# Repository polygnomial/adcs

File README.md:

# ADCS

## Docs

- Power Architecture
- RT1170 and RT1060 pin map
- slides and other notes
- Tim's review
- TODO move other notes here

## Hardware

### Soldermander

CPU (RT1170) + RAM (MRAM - SEMC and xSPI) + power breakout board, with 2x 100-pin board to board connectors.

### Sqrt of G

Eventual functional ADCS controller and sensor mainboard that the CPU board will sit on top of

### PCBranch

Development breakout board that breaks out all the pins of the RT1170 CPU

---

## Code

### flight

Rust code with a Teensy target, RT1170 target (not yet implemented), etc.

### cpp-code

Useful for checking that I implemented my Rust drivers correctly

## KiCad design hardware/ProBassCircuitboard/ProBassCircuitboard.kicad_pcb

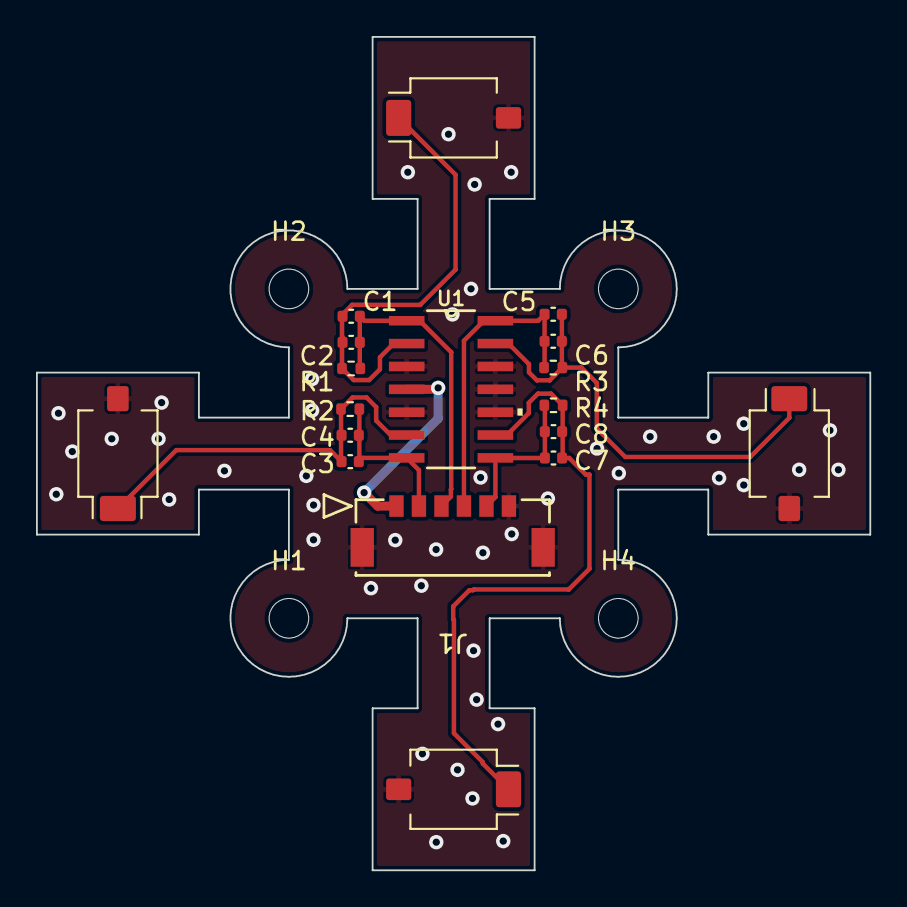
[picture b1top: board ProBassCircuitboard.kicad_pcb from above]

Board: 2 copper layers, 46.3 x 46.3 mm, 22 parts (0 on the bottom side), 10 nets.

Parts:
C1, C3, C5, C7: 1nF; C_0402_1005Metric
C2, C4, C6, C8: 100nF; C_0402_1005Metric
D1, D2, D3, D4: SFH2430; Osram_SFH2430
H1, H2, H3, H4: MountingHole_Pad; MountingHole_2.2mm_M2
J1: 5055670631; CON_5055670631
R1, R2, R3, R4: 3.9k; R_0402_1005Metric
U1: LTC2052IS_PBF; SO-14_S

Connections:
+3V3: J1.1, U1.4 (V+)
/OUT1: C1.2, C2.2, J1.3, R1.2, U1.1 (OUTA)
/OUT2: C3.2, C4.2, J1.2, R2.2, U1.7 (OUTB)
/OUT3: C7.2, C8.2, J1.5, R4.2, U1.8 (OUTC)
/OUT4: C5.2, C6.2, J1.4, R3.2, U1.14 (OUTD)
/Photodiode 1/IN-: C1.1, C2.1, D1.1 (K), R1.1, U1.2 (-INA)
/Photodiode 2/IN-: C3.1, C4.1, D2.1 (K), R2.1, U1.6 (-INB)
/Photodiode 3/IN-: C7.1, C8.1, D4.1 (K), R4.1, U1.9 (-INC)
/Photodiode 4/IN-: C5.1, C6.1, D3.1 (K), R3.1, U1.13 (-IND)
GND: D1.2 (A), D2.2 (A), D3.2 (A), D4.2 (A), J1.6, J1.7 (Shield), J1.8 (Shield), U1.3 (+INA), U1.5 (+INB), U1.10 (+INC), U1.11 (V-), U1.12 (+IND)

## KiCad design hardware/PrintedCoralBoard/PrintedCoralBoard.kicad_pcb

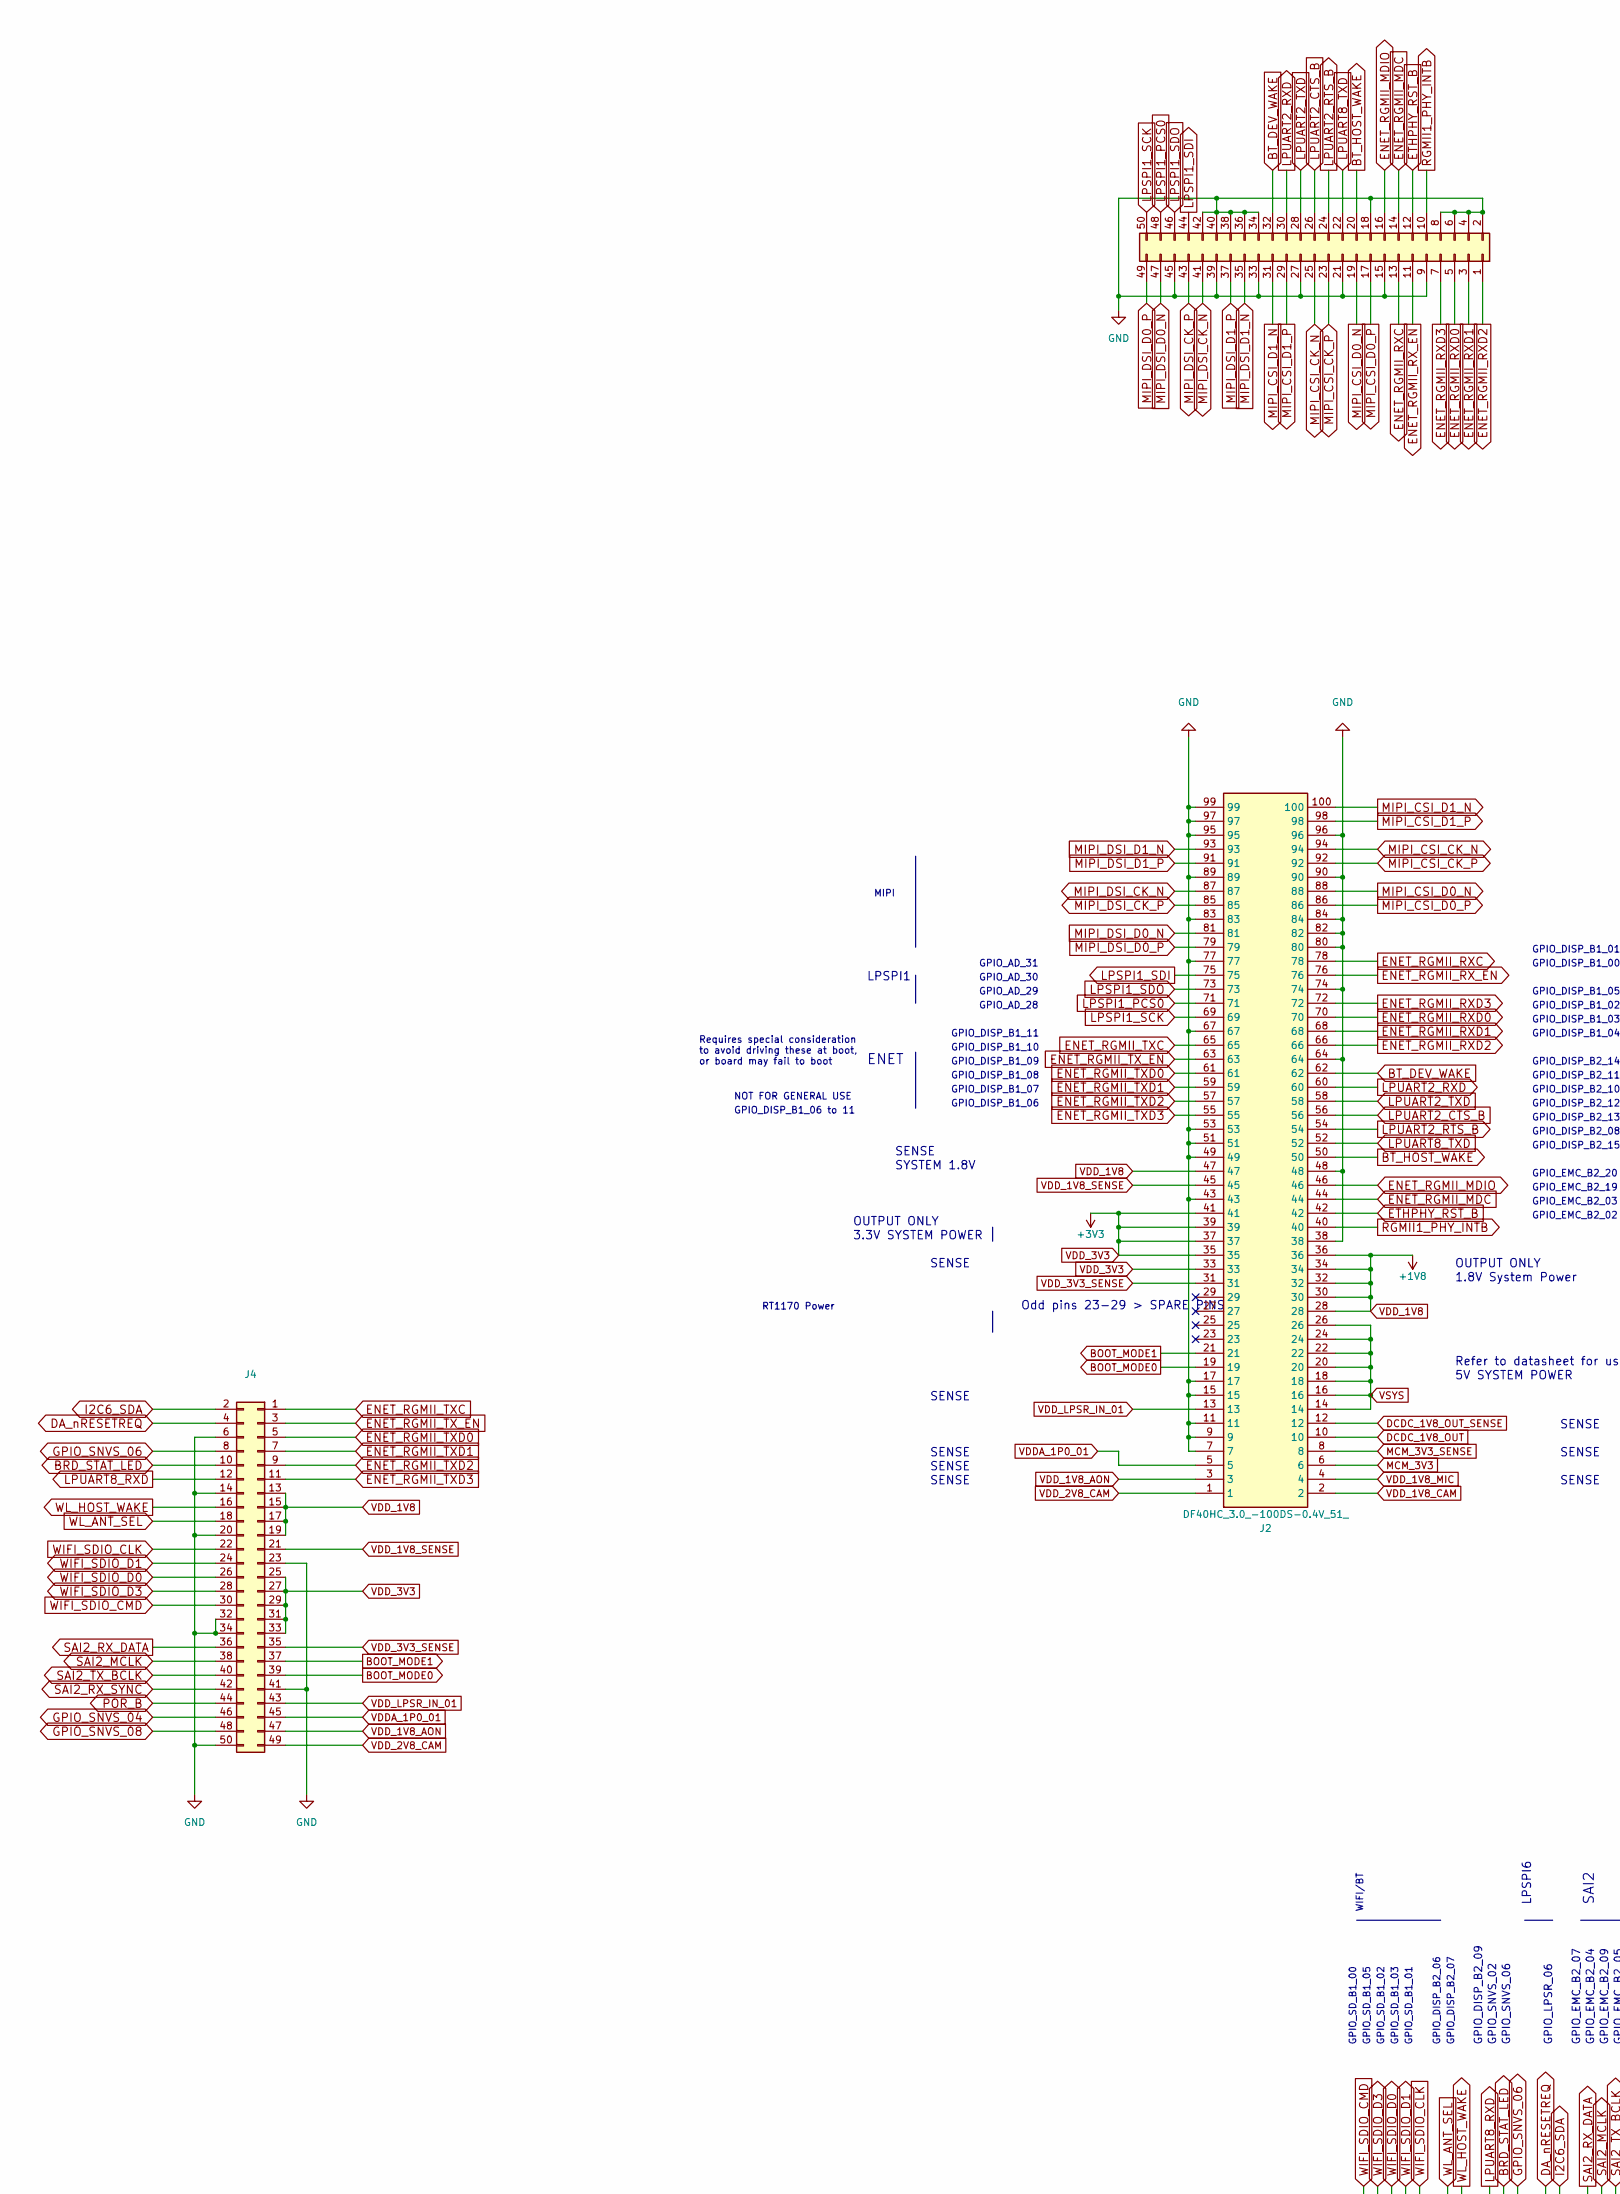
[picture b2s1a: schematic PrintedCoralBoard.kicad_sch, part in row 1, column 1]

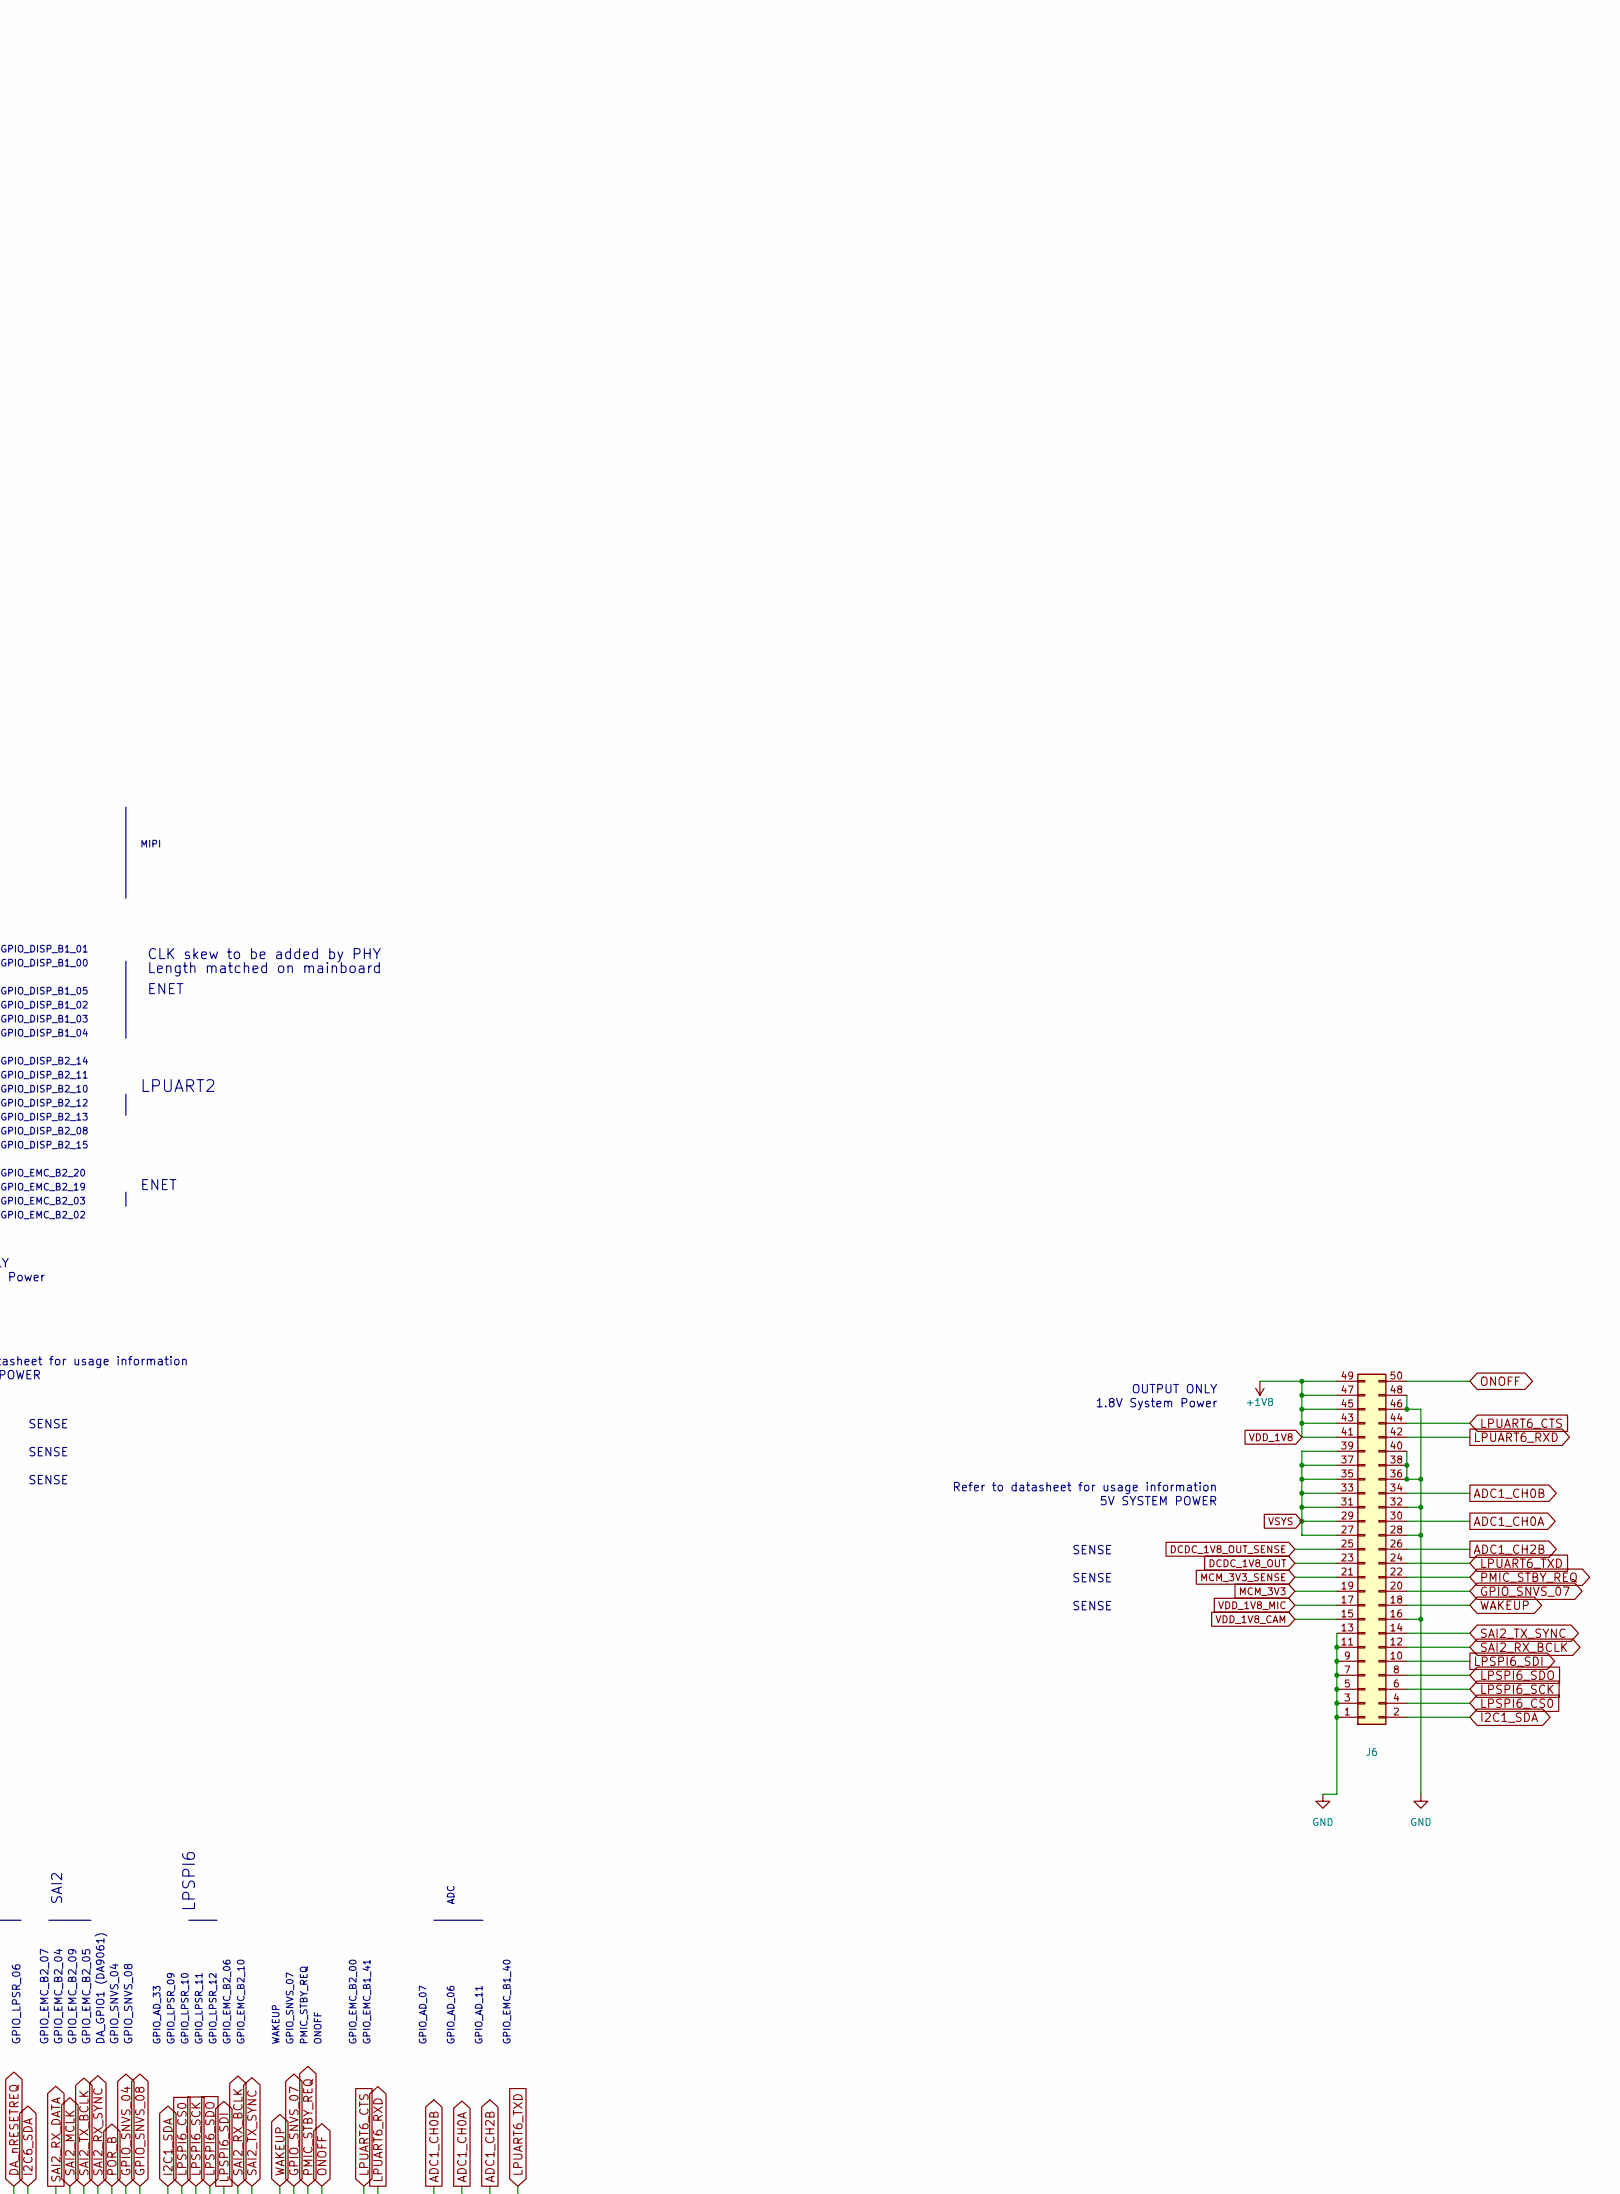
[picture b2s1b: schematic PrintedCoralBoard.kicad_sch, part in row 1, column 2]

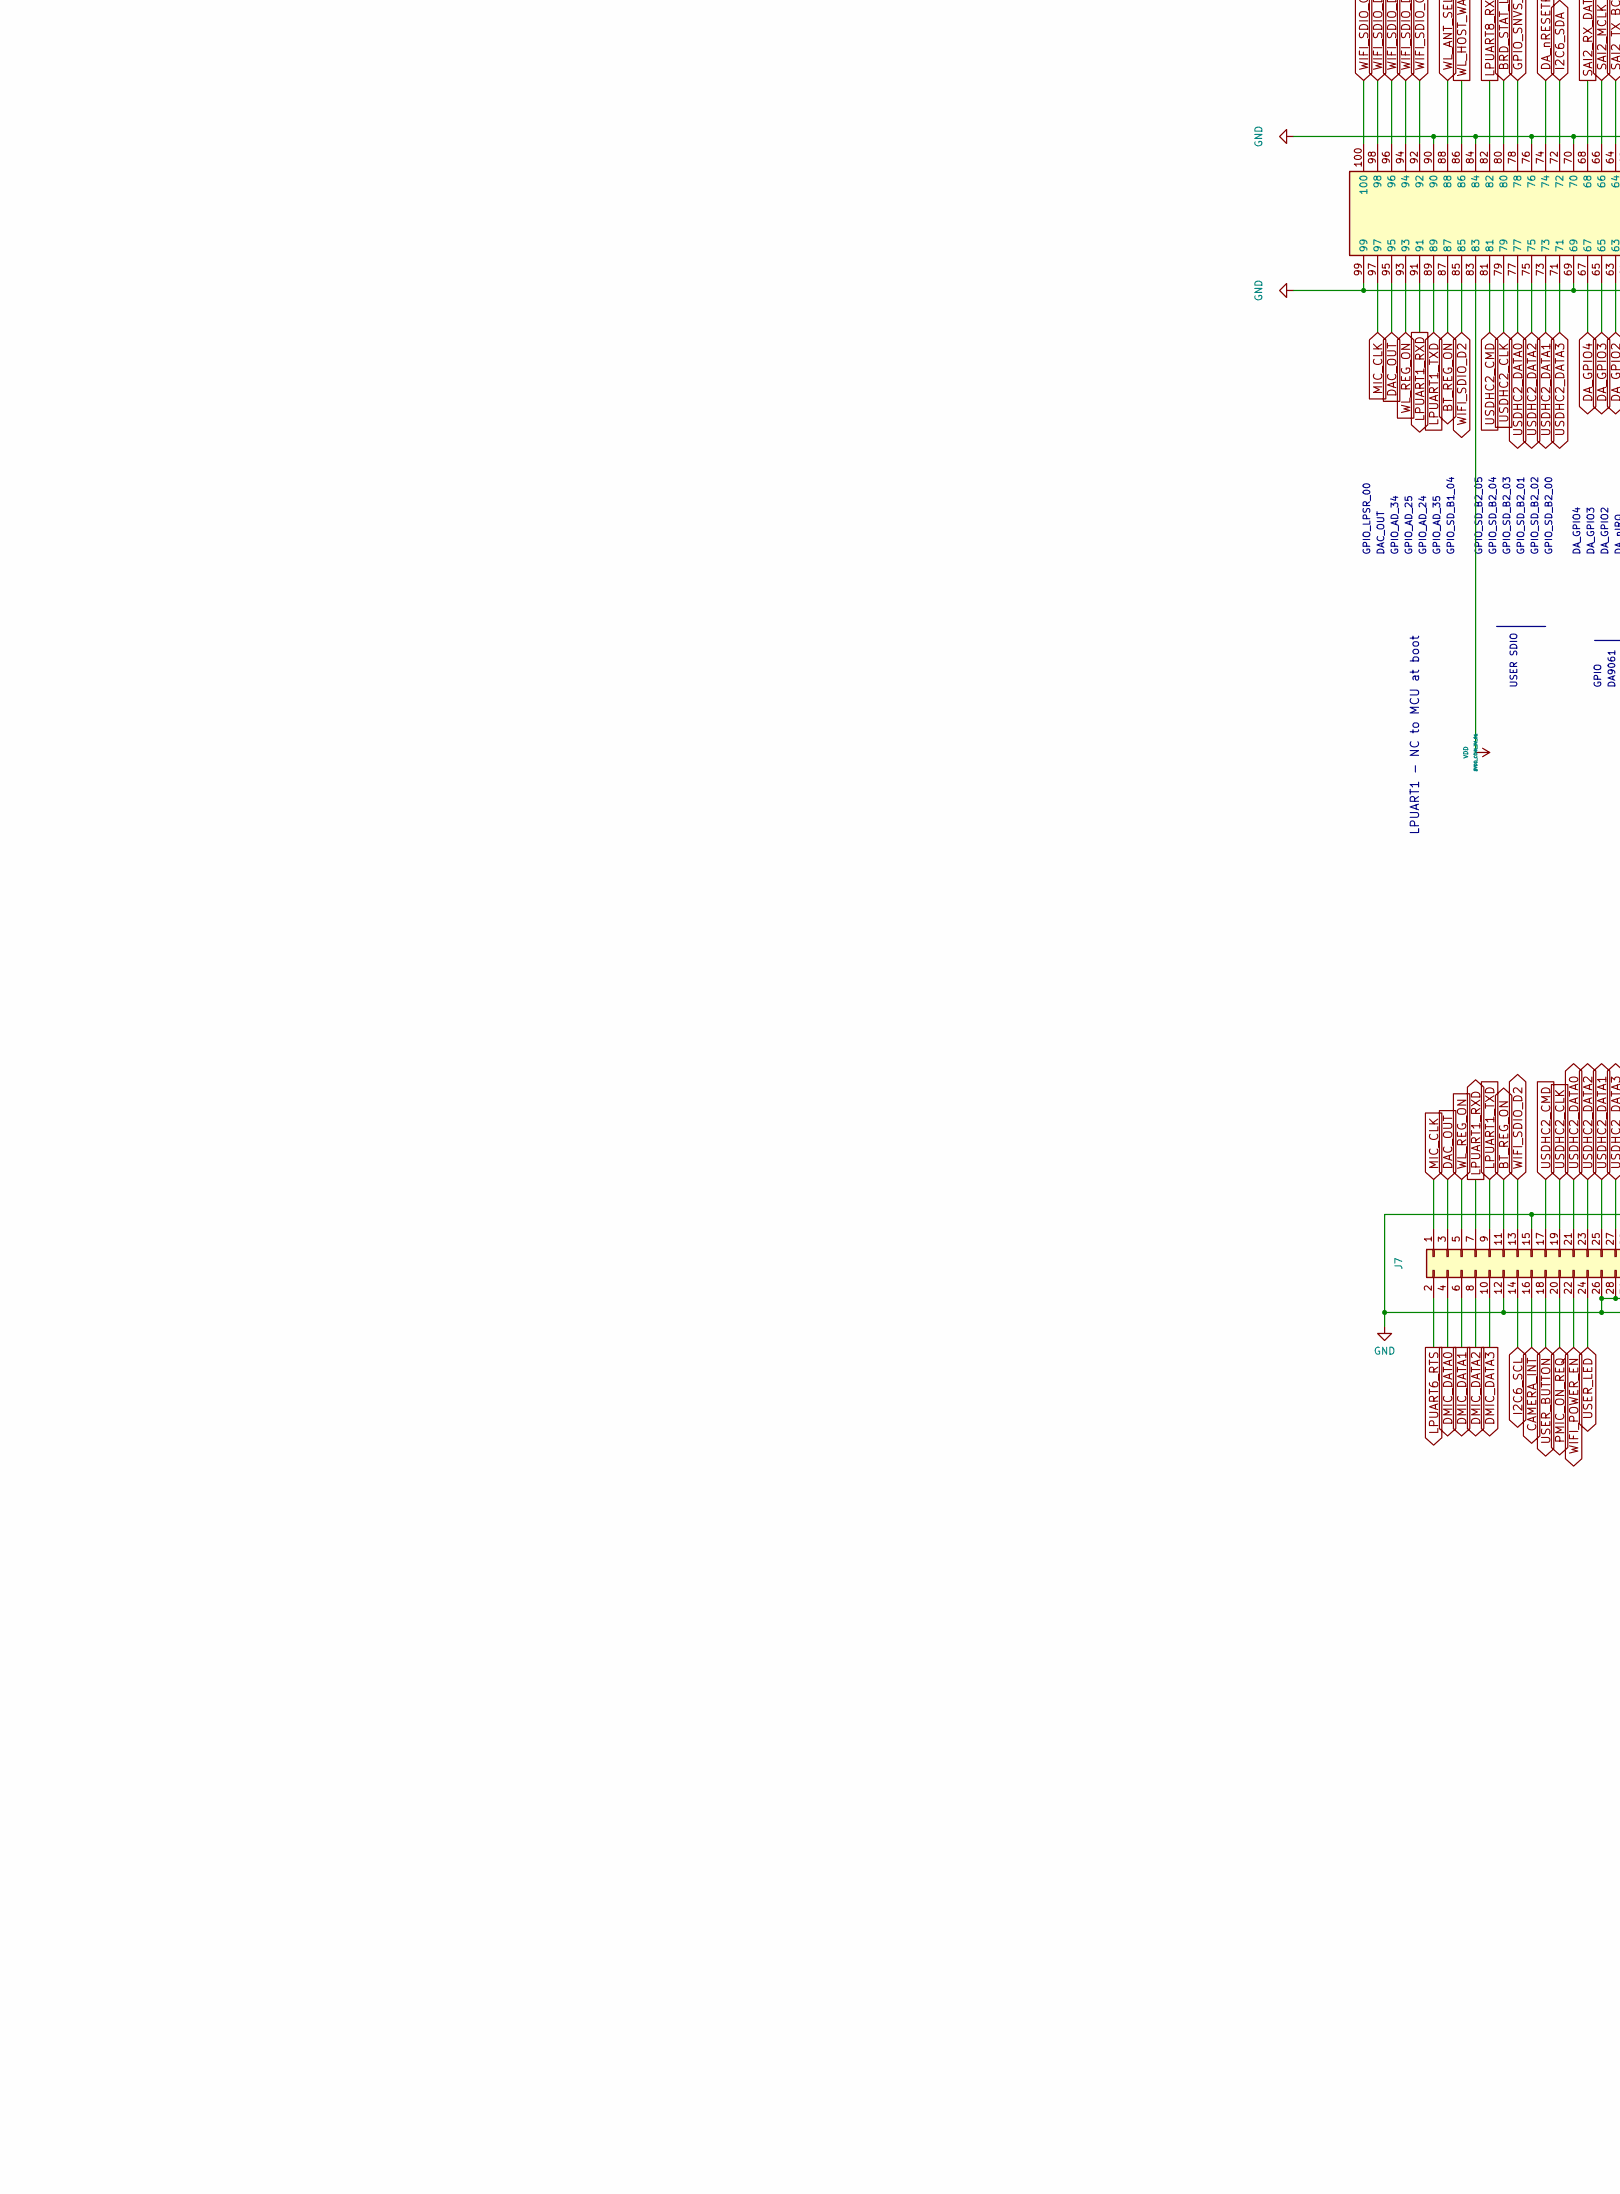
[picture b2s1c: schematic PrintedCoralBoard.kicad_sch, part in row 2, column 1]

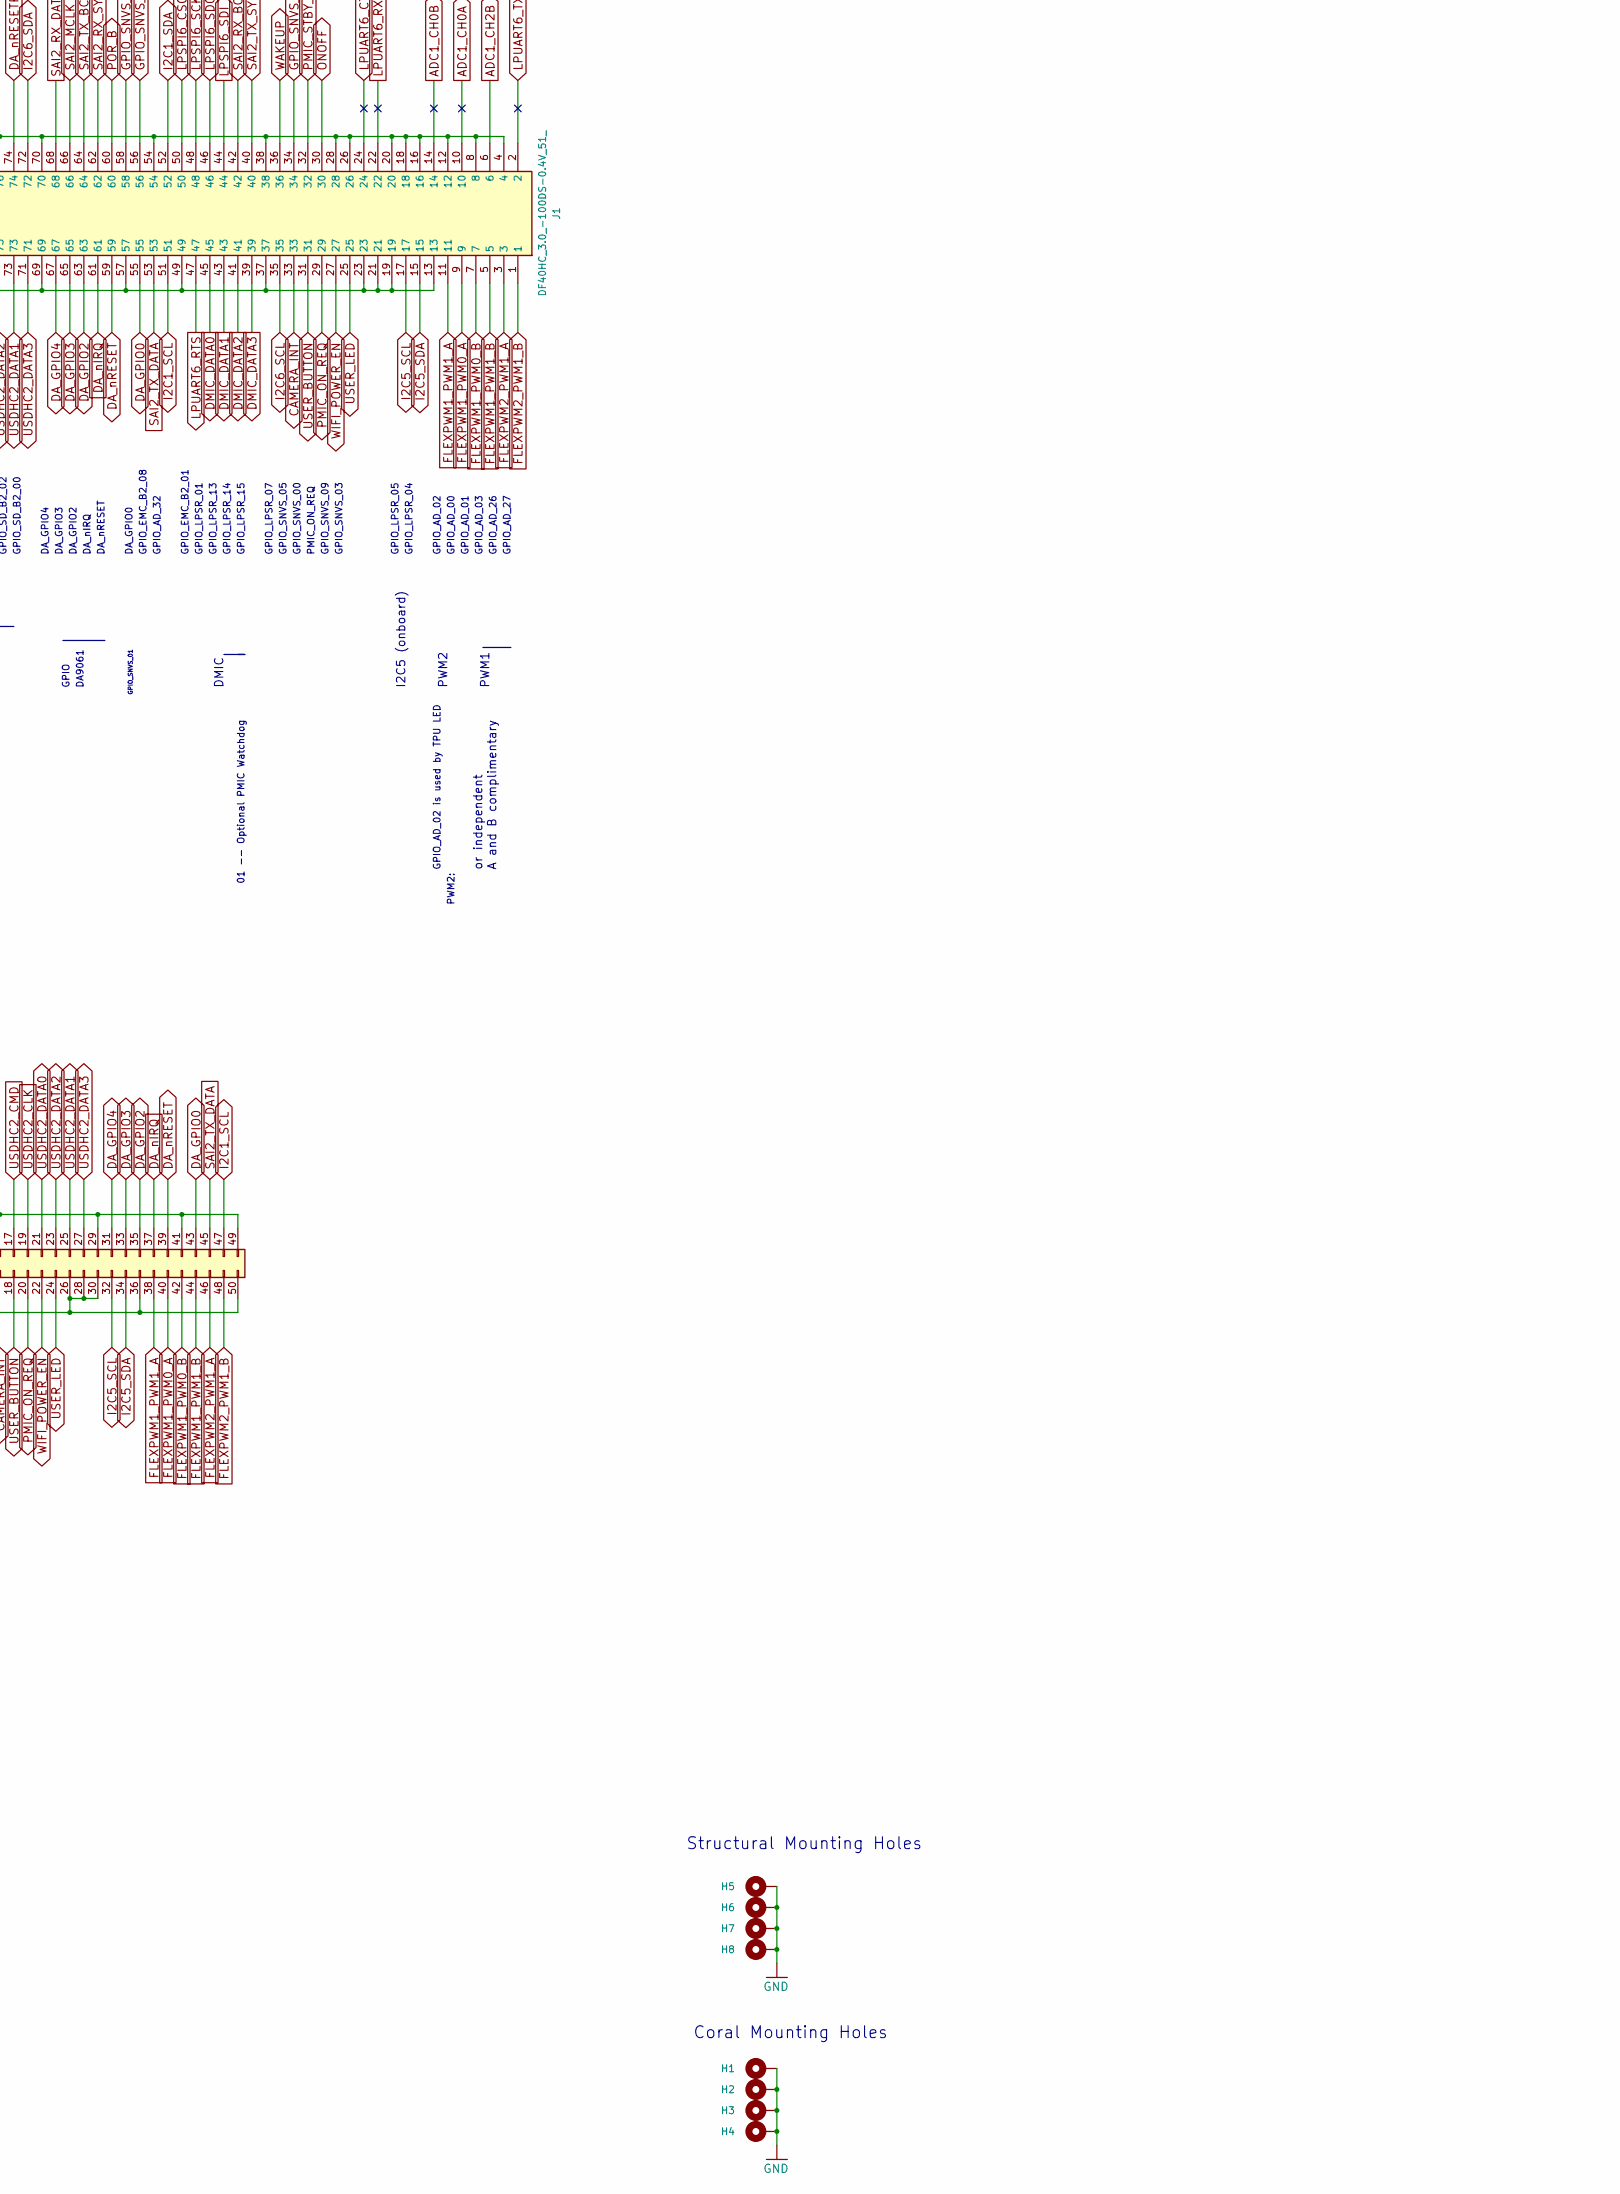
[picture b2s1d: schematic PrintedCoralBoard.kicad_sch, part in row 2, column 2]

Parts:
H1, H2, H3, H4: MountingHole_Pad; CoralLandingPad
H5, H6, H7, H8: MountingHole_Pad; MountingHole_3.2mm_M3_DIN965_Pad
J1, J2: DF40HC_3.0_-100DS-0.4V_51_; DF40HC30100DS04V51; Manufacturer_Part_Number DF40HC(3.0)-100DS-0.4V(51)
J4, J5, J6, J7: Conn_02x25_Odd_Even; PinHeader_2x25_P2.54mm_Vertical; LCSC Part Number C350296

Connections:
ADC1_CH0A: J1.10, J6.30
ADC1_CH0B: J1.14, J6.34
ADC1_CH2B: J1.6, J6.26
BOOT_MODE0: J2.19, J4.39
BOOT_MODE1: J2.21, J4.37
BRD_STAT_LED: J1.80, J4.10
BT_DEV_WAKE: J2.62, J5.32
BT_HOST_WAKE: J2.50, J5.20
BT_REG_ON: J1.87, J7.11
CAMERA_INT: J1.33, J7.16
DAC_OUT: J1.95, J7.3
DA_GPIO0: J1.55, J7.43
DA_GPIO2: J1.63, J7.35
DA_GPIO3: J1.65, J7.33
DA_GPIO4: J1.67, J7.31
DA_nIRQ: J1.61, J7.37
DA_nRESET: J1.59, J7.39
DA_nRESETREQ: J1.74, J4.4
DCDC_1V8_OUT: J2.10, J6.23
DCDC_1V8_OUT_SENSE: J2.12, J6.25
DMIC_DATA0: J1.45, J7.4
DMIC_DATA1: J1.43, J7.6
DMIC_DATA2: J1.41, J7.8
DMIC_DATA3: J1.39, J7.10
ENET_RGMII_MDC: J2.44, J5.14
ENET_RGMII_MDIO: J2.46, J5.16
ENET_RGMII_RXC: J2.78, J5.13
ENET_RGMII_RXD0: J2.70, J5.5
ENET_RGMII_RXD1: J2.68, J5.3
ENET_RGMII_RXD2: J2.66, J5.1
ENET_RGMII_RXD3: J2.72, J5.7
ENET_RGMII_RX_EN: J2.76, J5.11
ENET_RGMII_TXC: J2.65, J4.1
ENET_RGMII_TXD0: J2.61, J4.5
ENET_RGMII_TXD1: J2.59, J4.7
ENET_RGMII_TXD2: J2.57, J4.9
ENET_RGMII_TXD3: J2.55, J4.11
ENET_RGMII_TX_EN: J2.63, J4.3
ETHPHY_RST_B: J2.42, J5.12
FLEXPWM1_PWM0_A: J1.9, J7.40
FLEXPWM1_PWM0_B: J1.7, J7.42
FLEXPWM1_PWM1_A: J1.11, J7.38
FLEXPWM1_PWM1_B: J1.5, J7.44
FLEXPWM2_PWM1_A: J1.3, J7.46
FLEXPWM2_PWM1_B: J1.1, J7.48
GND: H1.1, H2.1, H3.1, H4.1, H5.1, H6.1, H7.1, H8.1, J1.4, J1.8, J1.12, J1.13, J1.16, J1.18, J1.19, J1.20, J1.21, J1.23, J1.26, J1.28, J1.37, J1.38, J1.49, J1.54, J1.57, J1.69, J1.70, J1.76, J1.84, J1.90, J1.99, J2.7, J2.9, J2.11, J2.15, J2.17, J2.38, J2.43, J2.48, J2.49, J2.51, J2.53, J2.64, J2.67, J2.74, J2.77, J2.80, J2.82, J2.83, J2.84, J2.89, J2.90, J2.95, J2.96, J2.97, J2.99, J4.6, J4.14, J4.20, J4.23, J4.32, J4.34, J4.41, J4.50, J5.2, J5.4, J5.6, J5.8, J5.9, J5.15, J5.18, J5.21, J5.27, J5.33, J5.34, J5.36, J5.38, J5.39, J5.40, J5.42, J5.45, J6.1, J6.3, J6.5, J6.7, J6.9, J6.11, J6.13, J6.16, J6.28, J6.32, J6.36, J6.38, J6.40, J6.46, J6.48, J7.12, J7.15, J7.26, J7.28, J7.29, J7.30, J7.36, J7.41, J7.49, J7.50
GPIO_SNVS_04: J1.58, J4.46
GPIO_SNVS_06: J1.78, J4.8
GPIO_SNVS_07: J1.34, J6.20
GPIO_SNVS_08: J1.56, J4.48
I2C1_SCL: J1.51, J7.47
I2C1_SDA: J1.52, J6.2
I2C5_SCL: J1.17, J7.32
I2C5_SDA: J1.15, J7.34
I2C6_SCL: J1.35, J7.14
I2C6_SDA: J1.72, J4.2
LPSPI1_PCS0: J2.71, J5.48
LPSPI1_SCK: J2.69, J5.50
LPSPI1_SDI: J2.75, J5.44
LPSPI1_SDO: J2.73, J5.46
LPSPI6_CS0: J1.50, J6.4
LPSPI6_SCK: J1.48, J6.6
LPSPI6_SDI: J1.44, J6.10
LPSPI6_SDO: J1.46, J6.8
LPUART1_RXD: J1.91, J7.7
LPUART1_TXD: J1.89, J7.9
LPUART2_CTS_B: J2.56, J5.26
LPUART2_RTS_B: J2.54, J5.24
LPUART2_RXD: J2.60, J5.30
LPUART2_TXD: J2.58, J5.28
LPUART6_CTS: J1.24, J6.44
LPUART6_RTS: J1.47, J7.2
LPUART6_RXD: J1.22, J6.42
LPUART6_TXD: J1.2, J6.24
LPUART8_RXD: J1.82, J4.12
LPUART8_TXD: J2.52, J5.22
MCM_3V3: J2.6, J6.19
MCM_3V3_SENSE: J2.8, J6.21
MIC_CLK: J1.97, J7.1
MIPI_CSI_CK_N: J2.94, J5.25
MIPI_CSI_CK_P: J2.92, J5.23
MIPI_CSI_D0_N: J2.88, J5.19
MIPI_CSI_D0_P: J2.86, J5.17
MIPI_CSI_D1_N: J2.100, J5.31
MIPI_CSI_D1_P: J2.98, J5.29
MIPI_DSI_CK_N: J2.87, J5.41
MIPI_DSI_CK_P: J2.85, J5.43
MIPI_DSI_D0_N: J2.81, J5.47
MIPI_DSI_D0_P: J2.79, J5.49
MIPI_DSI_D1_N: J2.93, J5.35
MIPI_DSI_D1_P: J2.91, J5.37
ONOFF: J1.30, J6.50
PMIC_ON_REQ: J1.29, J7.20
PMIC_STBY_REQ: J1.32, J6.22
POR_B: J1.60, J4.44
RGMII1_PHY_INTB: J2.40, J5.10
SAI2_MCLK: J1.66, J4.38
SAI2_RX_BCLK: J1.42, J6.12
SAI2_RX_DATA: J1.68, J4.36
SAI2_RX_SYNC: J1.62, J4.42
SAI2_TX_BCLK: J1.64, J4.40
SAI2_TX_DATA: J1.53, J7.45
SAI2_TX_SYNC: J1.40, J6.14
USDHC2_CLK: J1.79, J7.19
USDHC2_CMD: J1.81, J7.17
USDHC2_DATA0: J1.77, J7.21
USDHC2_DATA1: J1.73, J7.25
USDHC2_DATA2: J1.75, J7.23
USDHC2_DATA3: J1.71, J7.27
USER_BUTTON: J1.31, J7.18
USER_LED: J1.25, J7.24
VDD: J1.83
VDDA_1P0_01: J2.5, J4.45
VDD_1V8: J2.28, J2.30, J2.32, J2.34, J2.36, J2.47, J4.13, J4.15, J4.17, J4.19, J6.41, J6.43, J6.45, J6.47, J6.49
VDD_1V8_AON: J2.3, J4.47
VDD_1V8_CAM: J2.2, J6.15
VDD_1V8_MIC: J2.4, J6.17
VDD_1V8_SENSE: J2.45, J4.21
VDD_2V8_CAM: J2.1, J4.49
VDD_3V3: J2.33, J2.35, J2.37, J2.39, J2.41, J4.25, J4.27, J4.29, J4.31, J4.33
VDD_3V3_SENSE: J2.31, J4.35
VDD_LPSR_IN_01: J2.13, J4.43
VSYS: J2.14, J2.16, J2.18, J2.20, J2.22, J2.24, J2.26, J6.27, J6.29, J6.31, J6.33, J6.35, J6.37, J6.39
WAKEUP: J1.36, J6.18
WIFI_POWER_EN: J1.27, J7.22
WIFI_SDIO_CLK: J1.92, J4.22
WIFI_SDIO_CMD: J1.100, J4.30
WIFI_SDIO_D0: J1.96, J4.26
WIFI_SDIO_D1: J1.94, J4.24
WIFI_SDIO_D2: J1.85, J7.13
WIFI_SDIO_D3: J1.98, J4.28
WL_ANT_SEL: J1.88, J4.18
WL_HOST_WAKE: J1.86, J4.16
WL_REG_ON: J1.93, J7.5

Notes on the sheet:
SYSTEM 1.8V
GPIO_AD_03
SENSE
GPIO_DISP_B1_05
GPIO_SD_B2_05
GPIO_AD_29
Odd pins 23-29 > SPARE PINS
ONOFF
GPIO_AD_01
GPIO_AD_32
GPIO_AD_33
USER SDIO
GPIO_AD_27
GPIO_DISP_B1_03
GPIO_DISP_B2_08
GPIO_SNVS_08
GPIO_EMC_B2_19
GPIO_AD_26
GPIO_SNVS_09
GPIO_AD_28
GPIO_EMC_B1_41
GPIO_LPSR_05
GPIO_SD_B2_00
GPIO_SD_B1_03
GPIO_DISP_B2_11
GPIO_DISP_B2_13
GPIO_LPSR_00
GPIO_DISP_B2_10
GPIO_EMC_B2_10
GPIO_DISP_B2_07
Refer to datasheet for usage information
Coral Mounting Holes
NOT FOR GENERAL USE
DA_GPIO3
SAI2
GPIO_DISP_B1_07
GPIO_DISP_B2_06
GPIO_SD_B1_02
GPIO_LPSR_13
GPIO_EMC_B2_00

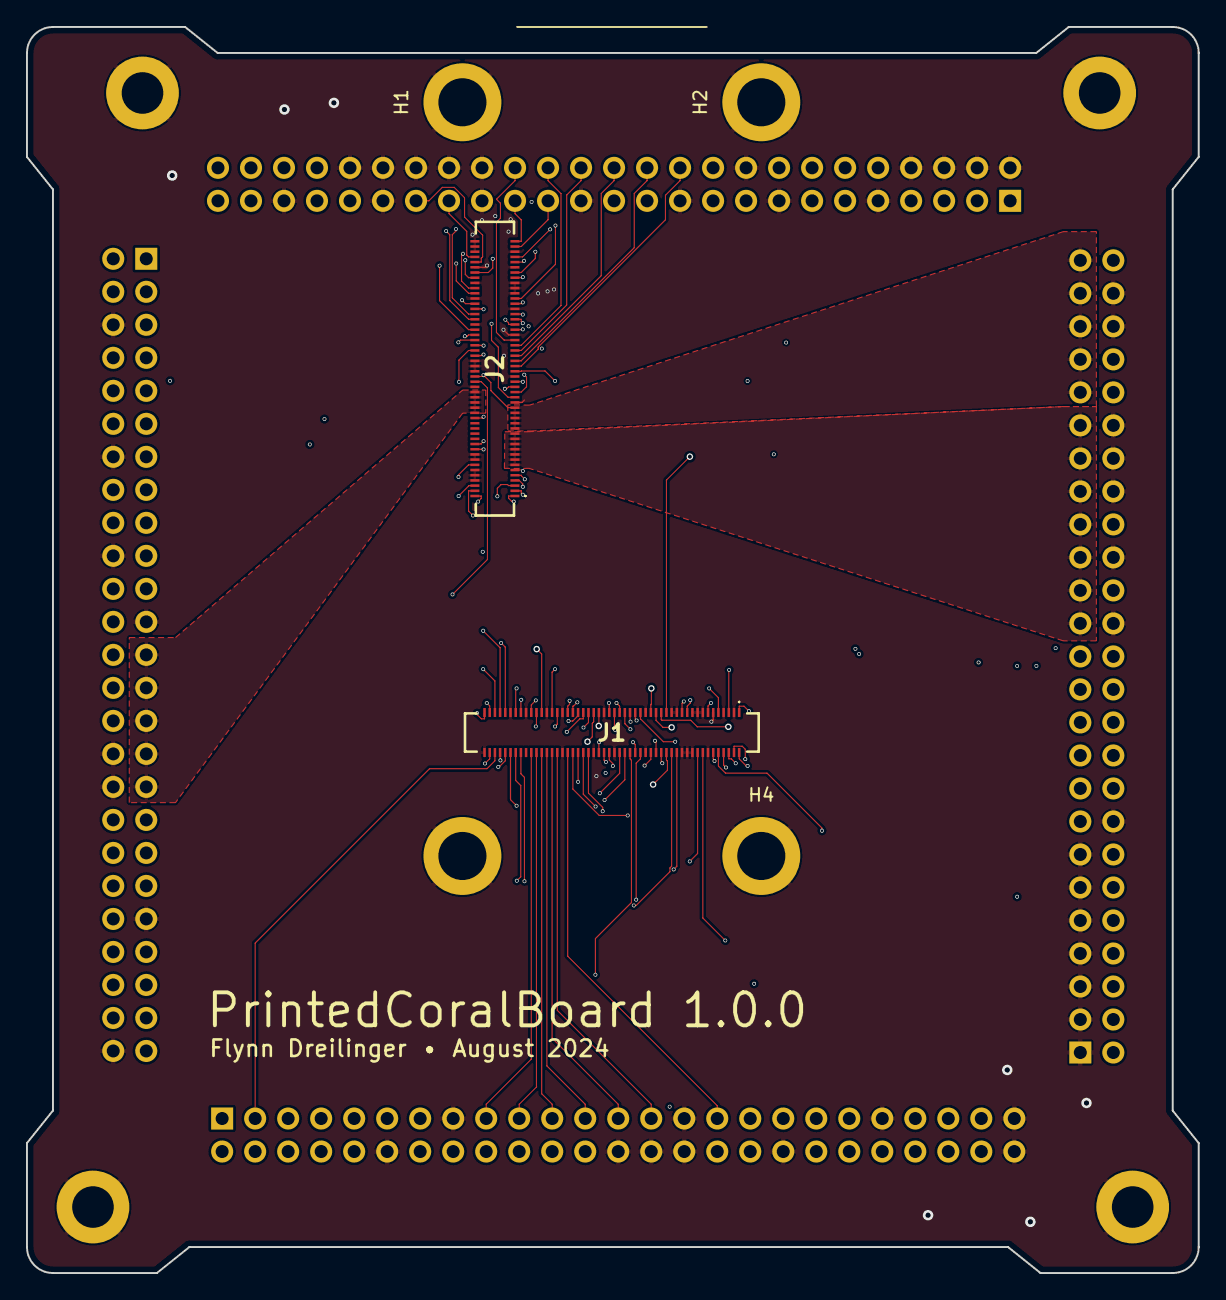
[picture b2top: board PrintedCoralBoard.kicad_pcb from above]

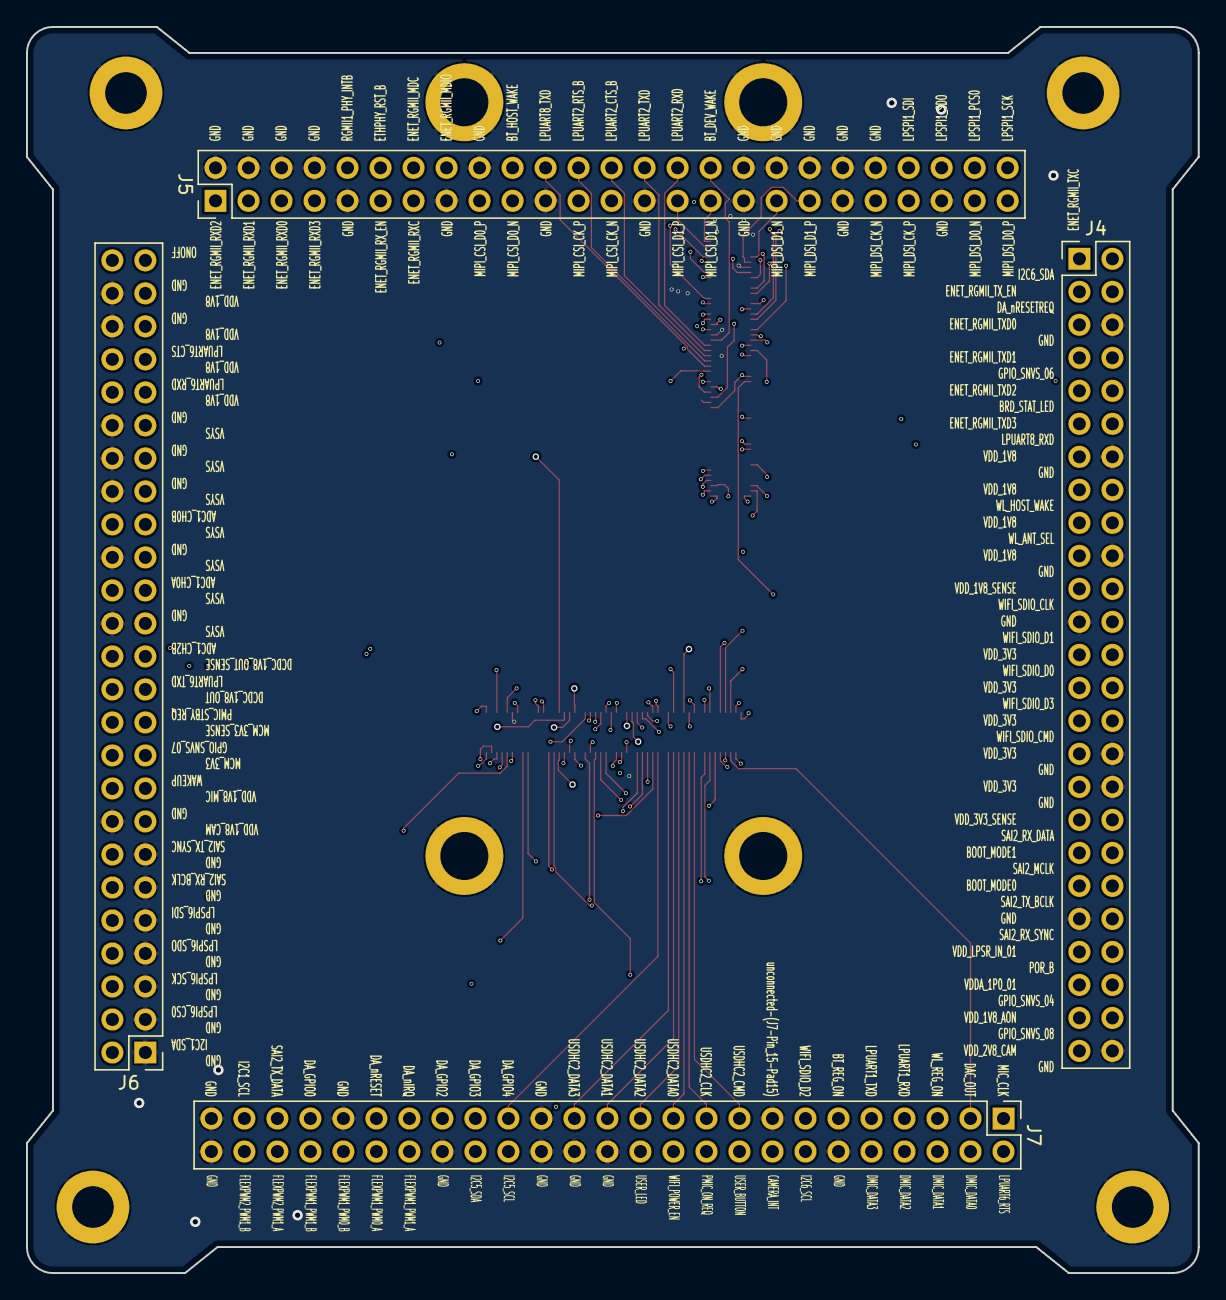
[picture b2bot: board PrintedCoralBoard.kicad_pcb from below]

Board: 4 copper layers, 90.2 x 95.9 mm, 14 parts (4 on the bottom side), 133 nets.
